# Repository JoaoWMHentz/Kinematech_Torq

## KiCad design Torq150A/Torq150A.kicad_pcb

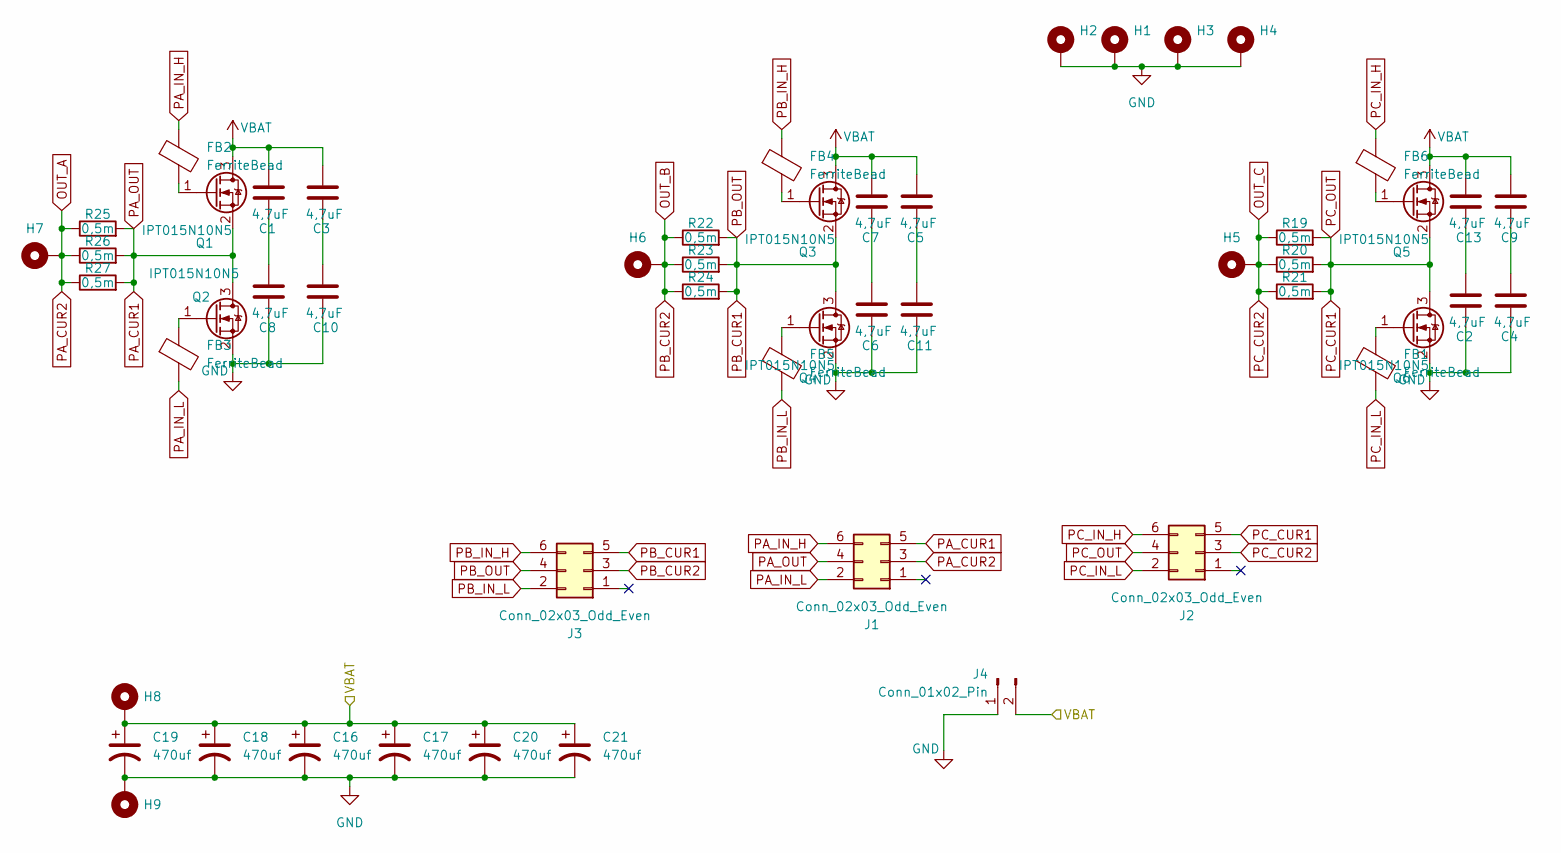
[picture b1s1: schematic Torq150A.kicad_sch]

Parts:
C1, C2, C3, C4, C5, C6, C7, C8, C9, C10, C11, C13: 4,7uF; C_1210_3225Metric
C16, C17, C18, C19, C20, C21: 470uf; CP_Radial_D16.0mm_P7.50mm
FB1, FB2, FB3, FB4, FB5, FB6: FerriteBead; L_Coilcraft_0805HQ_2012Metric
H1, H2, H3, H4: MountingHole_Pad; MountingHole_2.7mm_M2.5_ISO7380_Pad
H5, H6, H7, H8, H9: MountingHole_Pad; MountingHole_6.4mm_M6_Pad_Via
J1, J2, J3: Conn_02x03_Odd_Even; PinHeader_2x03_P2.54mm_Vertical
J4: Conn_01x02_Pin; PinSocket_1x02_P2.54mm_Vertical
Q1, Q2, Q3, Q4, Q5, Q6: IPT015N10N5; Infineon_PG-HSOF-8-1
R19, R20, R21, R22, R23, R24, R25, R26, R27: 0,5m; R_2512_6332Metric

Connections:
GND: C2.2, C4.2, C6.2, C8.2, C10.2, C11.2, C16.2, C17.2, C18.2, C19.2, C20.2, C21.2, H1.1, H2.1, H3.1, H4.1, H9.1, J4.1, Q2.2 (S), Q4.2 (S), Q6.2 (S)
unnamed: C1.2, C8.1
unnamed: C4.1, C9.2
unnamed: C6.1, C7.2
unnamed: C3.2, C10.1
unnamed: C5.2, C11.1
unnamed: C2.1, C13.2
unnamed: FB2.2, Q1.1 (G)
unnamed: FB3.1, Q2.1 (G)
unnamed: FB4.2, Q3.1 (G)
unnamed: FB5.1, Q4.1 (G)
unnamed: FB6.2, Q5.1 (G)
unnamed: FB1.1, Q6.1 (G)
OUT_A: H7.1, J1.3, R25.1, R26.1, R27.1
OUT_B: H6.1, J3.3, R22.1, R23.1, R24.1
OUT_C: H5.1, J2.3, R19.1, R20.1, R21.1
PA_CUR1: J1.4, J1.5, Q1.2 (S), Q2.3 (D), R25.2, R26.2, R27.2
PA_IN_H: FB2.1, J1.6
PA_IN_L: FB3.2, J1.2
PB_CUR1: J3.4, J3.5, Q3.2 (S), Q4.3 (D), R22.2, R23.2, R24.2
PB_IN_H: FB4.1, J3.6
PB_IN_L: FB5.2, J3.2
PC_CUR1: J2.4, J2.5, Q5.2 (S), Q6.3 (D), R19.2, R20.2, R21.2
PC_IN_H: FB6.1, J2.6
PC_IN_L: FB1.2, J2.2
VBAT: C1.1, C3.1, C5.1, C7.1, C9.1, C13.1, C16.1, C17.1, C18.1, C19.1, C20.1, C21.1, H8.1, J4.2, Q1.3 (D), Q3.3 (D), Q5.3 (D)

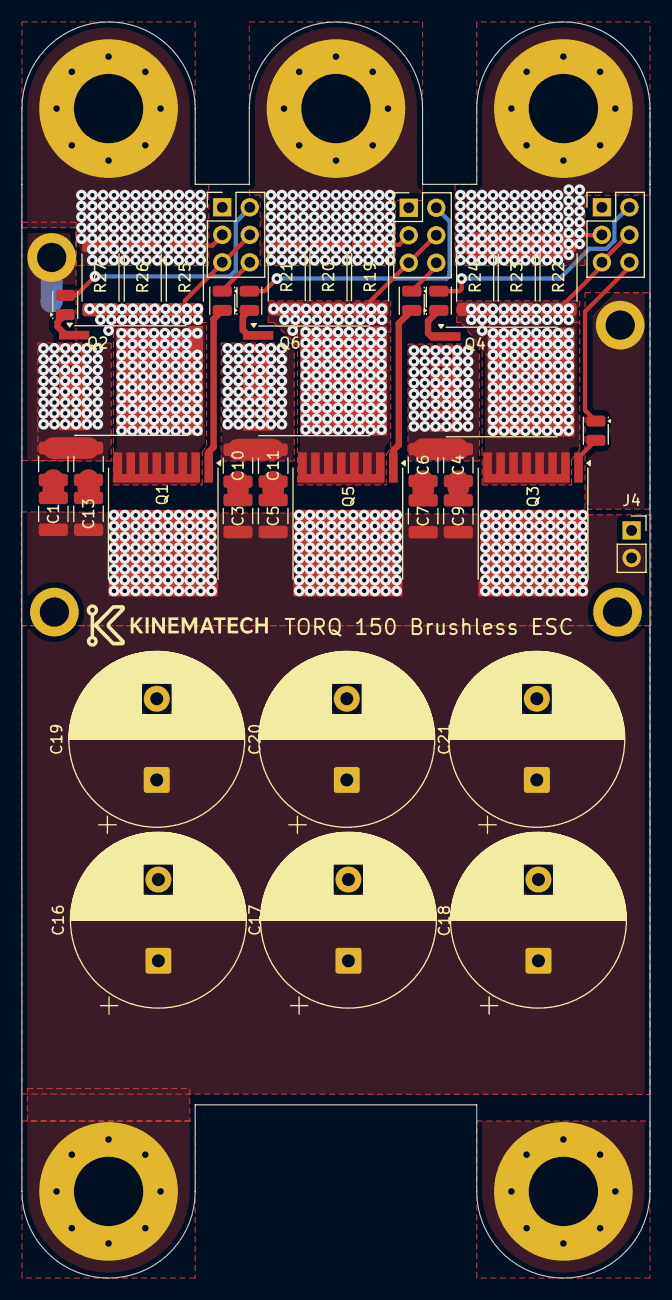
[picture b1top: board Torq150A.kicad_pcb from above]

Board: 2 copper layers, 58.0 x 116.0 mm, 52 parts (0 on the bottom side), 26 nets.

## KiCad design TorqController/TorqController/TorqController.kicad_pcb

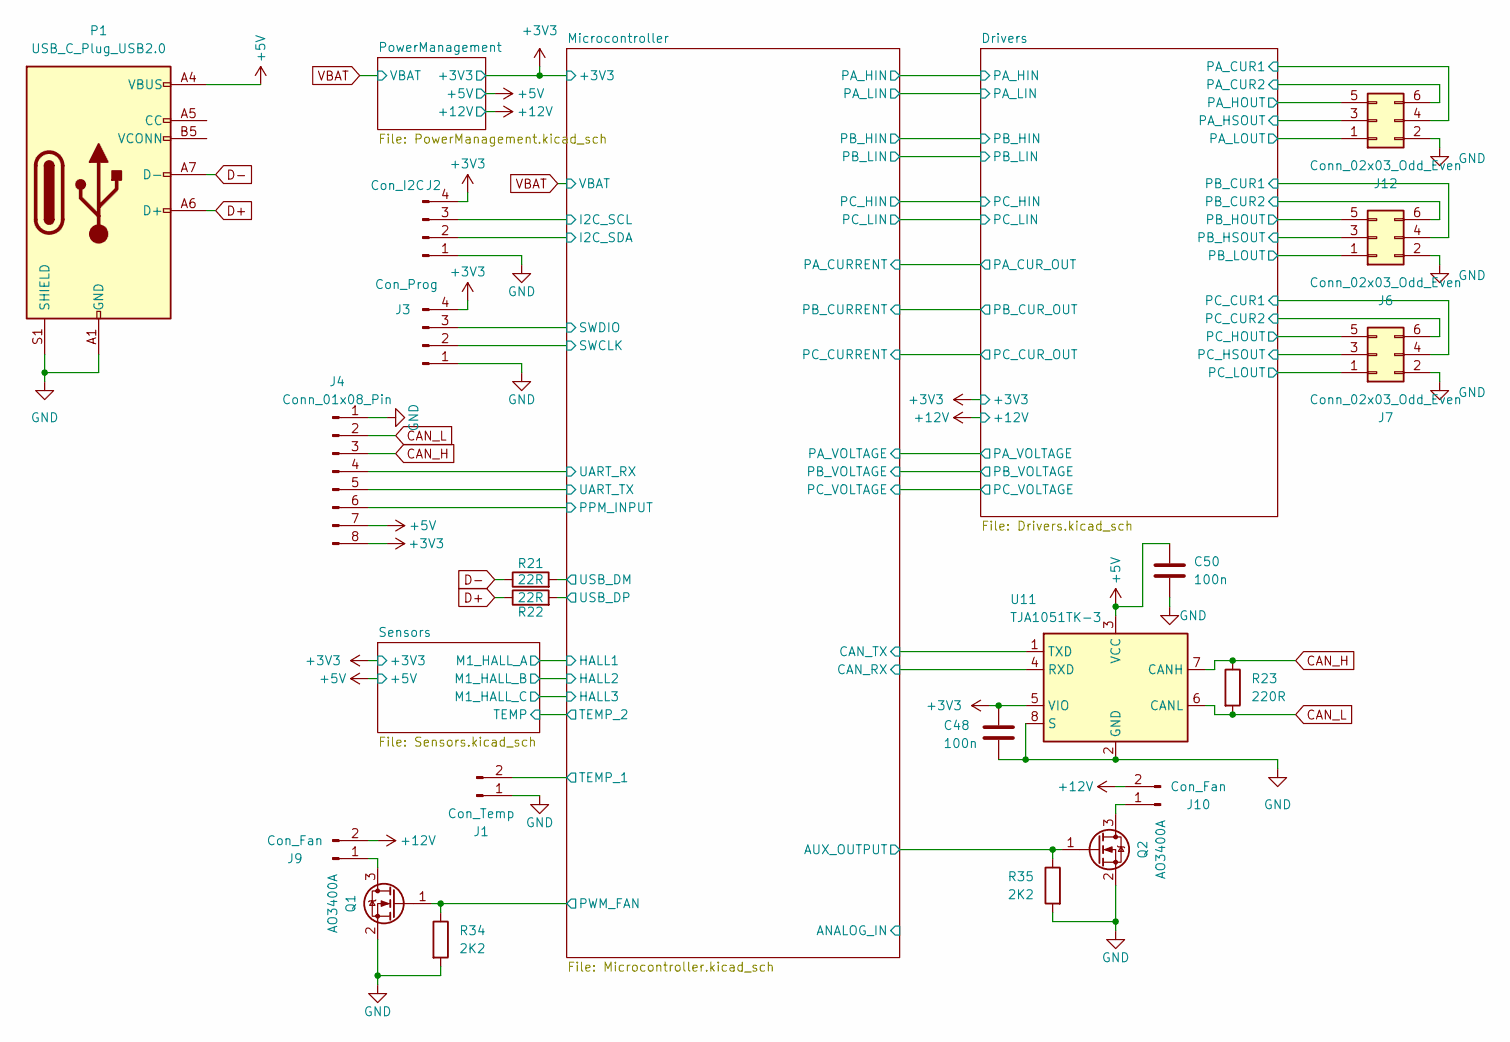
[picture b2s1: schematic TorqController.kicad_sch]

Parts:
C48, C50: 100n; C_0402_1005Metric
J1: Con_Temp; JST_EH_B2B-EH-A_1x02_P2.50mm_Vertical
J2: Con_I2C; JST_EH_B4B-EH-A_1x04_P2.50mm_Vertical
J3: Con_Prog; JST_EH_B4B-EH-A_1x04_P2.50mm_Vertical
J4: Conn_01x08_Pin; JST_EH_B8B-EH-A_1x08_P2.50mm_Vertical
J6, J7, J12: Conn_02x03_Odd_Even; PinHeader_2x03_P2.54mm_Vertical
J9, J10: Con_Fan; JST_EH_B2B-EH-A_1x02_P2.50mm_Vertical
P1: USB_C_Plug_USB2.0; USB_C_Receptacle_G-Switch_GT-USB-7010ASV
Q1, Q2: AO3400A; SOT-23
R21, R22: 22R; R_0402_1005Metric
R23: 220R; R_0402_1005Metric
R34, R35: 2K2; R_0402_1005Metric
U11: TJA1051TK-3; HVSON-8-1EP_3x3mm_P0.65mm_EP1.6x2.4mm

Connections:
+3V3: C48.1, J2.4, J3.4, J4.8, U11.5 (VIO); also elsewhere on the board
+5V: C50.1, J4.7, P1.A4 (VBUS), P1.A9 (VBUS), P1.B4 (VBUS), P1.B9 (VBUS), U11.3 (VCC); also elsewhere on the board
+12V: J9.2, J10.2; also elsewhere on the board
/Drivers/PA_CUR1: J12.4; also elsewhere on the board
/Drivers/PA_CUR2: J12.6; also elsewhere on the board
/Drivers/PA_HOUT: J12.5; also elsewhere on the board
/Drivers/PA_HSOUT: J12.3; also elsewhere on the board
/Drivers/PA_LOUT: J12.1; also elsewhere on the board
/Drivers/PB_CUR1: J6.4; also elsewhere on the board
/Drivers/PB_CUR2: J6.6; also elsewhere on the board
/Drivers/PB_HOUT: J6.5; also elsewhere on the board
/Drivers/PB_HSOUT: J6.3; also elsewhere on the board
/Drivers/PB_LOUT: J6.1; also elsewhere on the board
/Drivers/PC_CUR1: J7.4; also elsewhere on the board
/Drivers/PC_CUR2: J7.6; also elsewhere on the board
/Drivers/PC_HOUT: J7.5; also elsewhere on the board
/Drivers/PC_HSOUT: J7.3; also elsewhere on the board
/Drivers/PC_LOUT: J7.1; also elsewhere on the board
/Microcontroller/AUX_OUTPUT: Q2.1 (G), R35.1; also elsewhere on the board
/Microcontroller/CAN_RX: U11.4 (RXD); also elsewhere on the board
/Microcontroller/CAN_TX: U11.1 (TXD); also elsewhere on the board
/Microcontroller/I2C_SCL: J2.3; also elsewhere on the board
/Microcontroller/I2C_SDA: J2.2; also elsewhere on the board
/Microcontroller/PPM_INPUT: J4.6; also elsewhere on the board
/Microcontroller/PWM_FAN: Q1.1 (G), R34.1; also elsewhere on the board
/Microcontroller/SWCLK: J3.2; also elsewhere on the board
/Microcontroller/SWDIO: J3.3; also elsewhere on the board
/Microcontroller/UART_RX: J4.4; also elsewhere on the board
/Microcontroller/UART_TX: J4.5; also elsewhere on the board
/Microcontroller/USB_DM: R21.2; also elsewhere on the board
/Microcontroller/USB_DP: R22.2; also elsewhere on the board
CAN_H: J4.3, R23.1, U11.7 (CANH)
CAN_L: J4.2, R23.2, U11.6 (CANL)
D+: P1.A6 (D+), R22.1
D-: P1.A7 (D-), R21.1
GND: C48.2, C50.2, J1.1, J2.1, J3.1, J4.1, J6.2, J7.2, J12.2, P1.A1 (GND), P1.A12 (GND), P1.B1 (GND), P1.B12 (GND), P1.S1 (SHIELD), Q1.2 (S), Q2.2 (S), R34.2, R35.2, U11.2 (GND), U11.8 (S), U11.9 (GND); also elsewhere on the board
unnamed: J9.1, Q1.3 (D)
unnamed: J10.1, Q2.3 (D)
Temp_1: J1.2; also elsewhere on the board

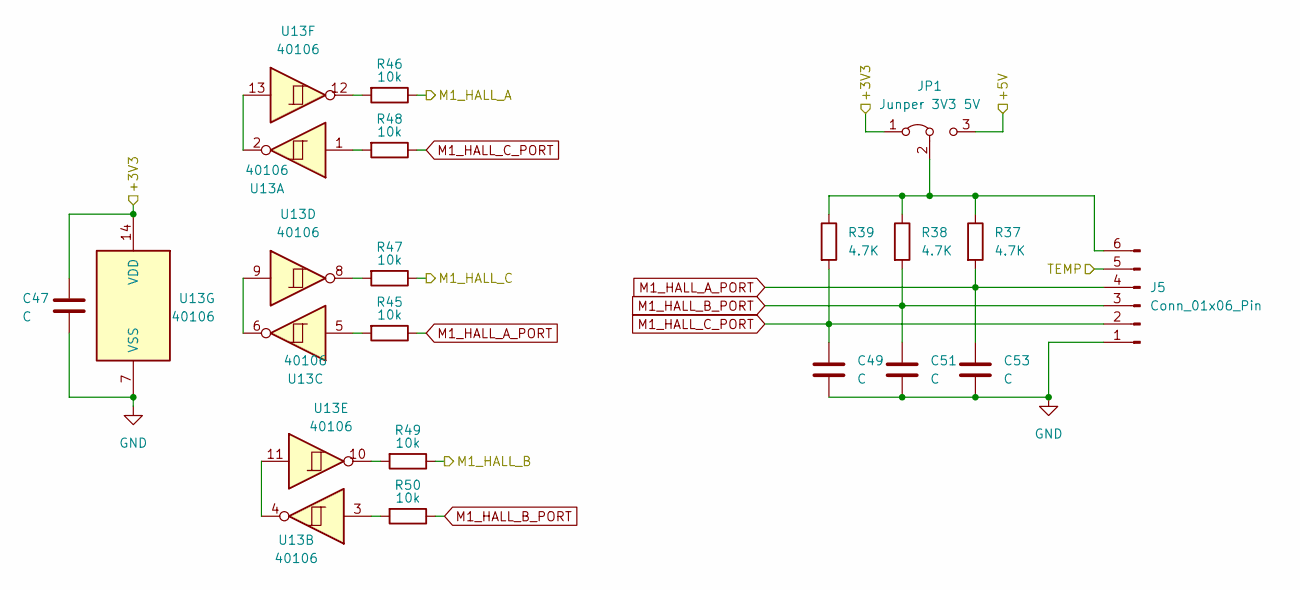
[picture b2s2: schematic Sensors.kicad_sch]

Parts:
C47, C49, C51, C53: C; C_0402_1005Metric
J5: Conn_01x06_Pin; JST_EH_B6B-EH-A_1x06_P2.50mm_Vertical
JP1: Junper 3V3 5V; SolderJumper-3_P1.3mm_Open_RoundedPad1.0x1.5mm_NumberLabels
R37, R38, R39: 4.7K; R_0402_1005Metric
R45, R46, R47, R48, R49, R50: 10k; R_0402_1005Metric
U13: 40106; DIP-14_W7.62mm_SMDSocket_SmallPads

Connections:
+3V3: C47.1, JP1.1 (A), U13.14 (VDD); also elsewhere on the board
/Microcontroller/HALL1: R46.1; also elsewhere on the board
/Microcontroller/HALL2: R49.1; also elsewhere on the board
/Microcontroller/HALL3: R47.1; also elsewhere on the board
GND: C47.2, C49.2, C51.2, C53.2, J5.1, U13.7 (VSS); also elsewhere on the board
M1_HALL_A_PORT: C53.1, J5.4, R37.2, R45.1
M1_HALL_B_PORT: C51.1, J5.3, R38.2, R50.1
M1_HALL_C_PORT: C49.1, J5.2, R39.2, R48.1
unnamed 60: J5.6, JP1.2 (C), R37.1, R38.1, R39.1; also elsewhere on the board
unnamed: R45.2, U13.5
unnamed: R46.2, U13.12
unnamed: R47.2, U13.8
unnamed: R48.2, U13.1
unnamed: R49.2, U13.10
unnamed: R50.2, U13.3
unnamed: U13.6, U13.9
unnamed: U13.4, U13.11
unnamed: U13.2, U13.13
Temp_2: J5.5; also elsewhere on the board

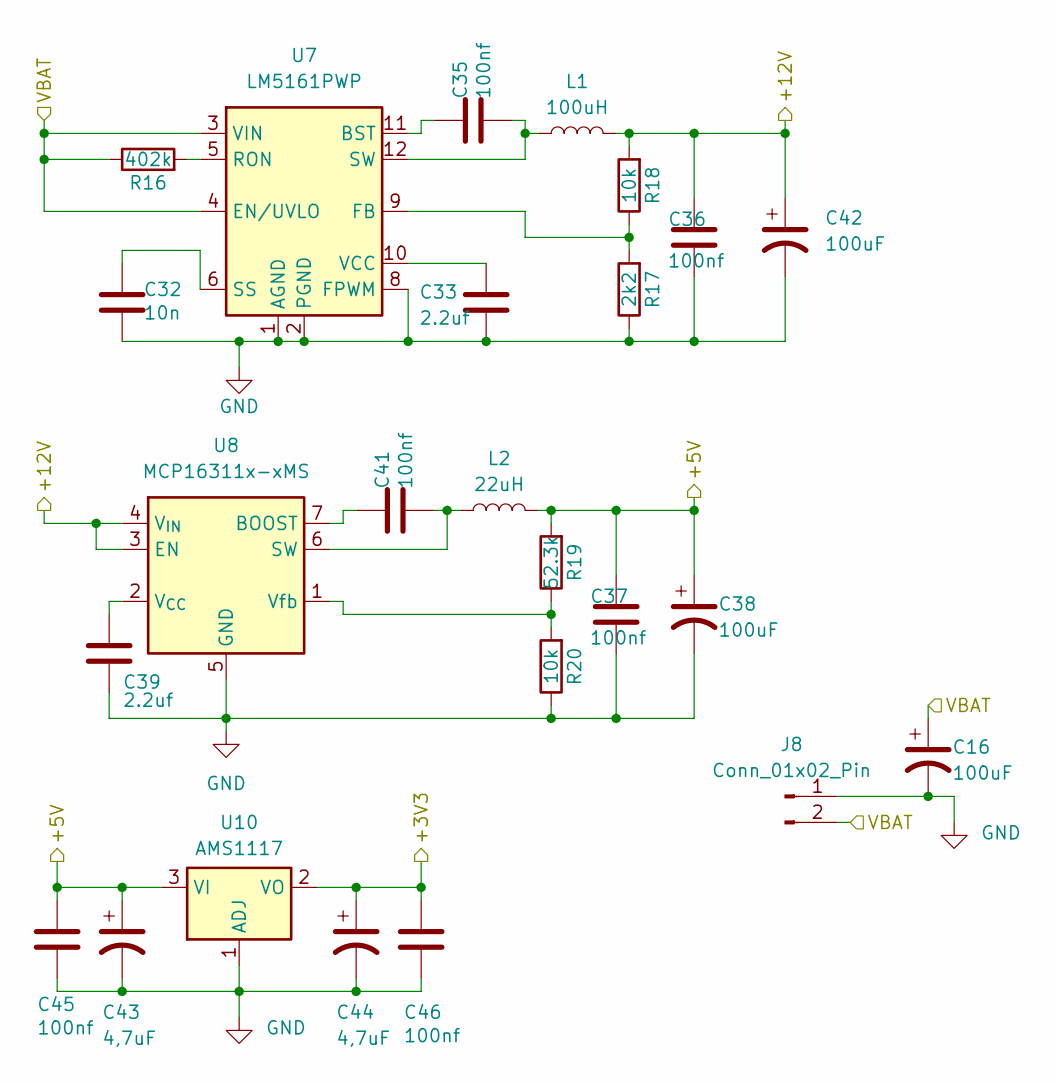
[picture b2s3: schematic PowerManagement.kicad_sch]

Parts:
C16, C38, C42: 100uF; CP_Elec_3x5.4
C32: 10n; C_0402_1005Metric
C33, C39: 2.2uf; C_0603_1608Metric
C35, C36, C37, C41, C45, C46: 100nf; C_0402_1005Metric
C43, C44: 4,7uF; CP_EIA-3216-10_Kemet-I
J8: Conn_01x02_Pin; PinHeader_1x02_P2.54mm_Vertical
L1: 100uH; L_KOHERelec_MDA5030
L2: 22uH; L_Chilisin_BMRB00050518-B
R16: 402k; R_0402_1005Metric
R17: 2k2; R_0402_1005Metric
R18, R20: 10k; R_0402_1005Metric
R19: 52.3k; R_0402_1005Metric
U7: LM5161PWP; Texas_HTSSOP-14-1EP_4.4x5mm_P0.65mm_EP3.4x5mm_Mask3.155x3.2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
U8: MCP16311x-xMS; MSOP-8_3x3mm_P0.65mm
U10: AMS1117; SOT-223-3_TabPin2

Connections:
+3V3: C44.1, C46.1, U10.2 (VO); also elsewhere on the board
+5V: C37.2, C38.1, C43.1, C45.1, L2.2, R19.2, U10.3 (VI); also elsewhere on the board
+12V: C36.2, C42.1, L1.2, R18.2, U8.3 (EN), U8.4 (V_{IN}); also elsewhere on the board
GND: C16.2, C32.2, C33.2, C36.1, C37.1, C38.2, C39.2, C42.2, C43.2, C44.2, C45.2, C46.2, J8.1, R17.1, R20.1, U7.1 (AGND), U7.2 (PGND), U7.8 (FPWM), U7.15 (AGND), U8.5 (GND), U8.8 (GND), U10.1 (ADJ); also elsewhere on the board
unnamed: C35.2, L1.1, U7.12 (SW), U7.13 (SW)
unnamed: C35.1, U7.11 (BST)
unnamed: R17.2, R18.1, U7.9 (FB)
unnamed: R16.2, U7.5 (RON)
unnamed: C32.1, U7.6 (SS)
unnamed: C33.1, U7.10 (VCC)
unnamed: C41.1, U8.7 (BOOST)
unnamed: C41.2, L2.1, U8.6 (SW)
unnamed: C39.1, U8.2 (V_{CC})
unnamed: R19.1, R20.2, U8.1 (Vfb)
VBAT: C16.1, J8.2, R16.1, U7.3 (VIN), U7.4 (EN/UVLO); also elsewhere on the board

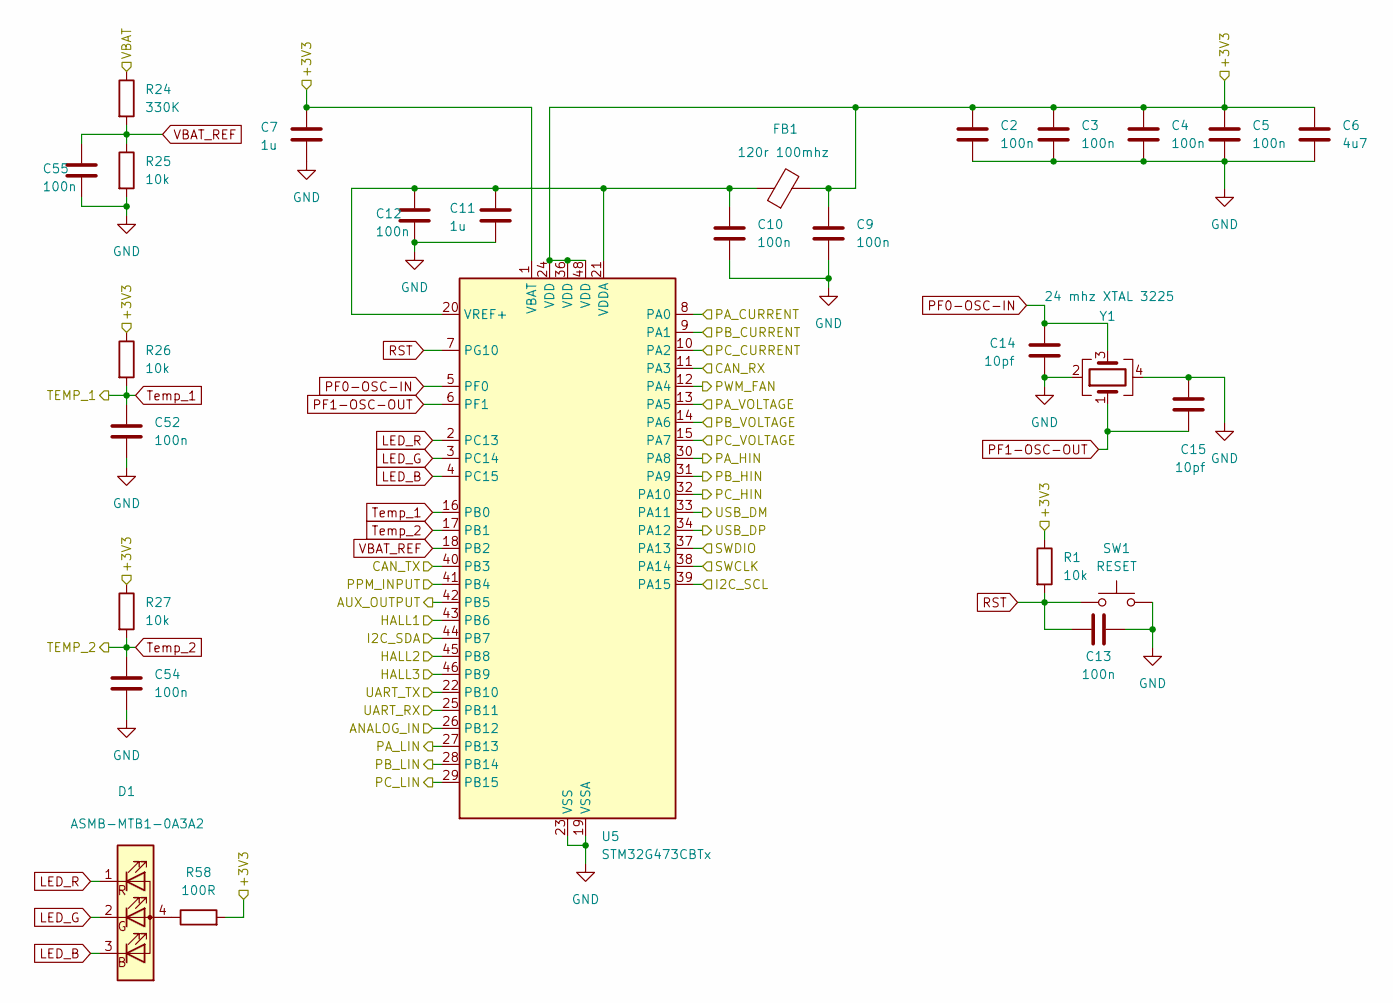
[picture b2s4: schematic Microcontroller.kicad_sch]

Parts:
C2, C3, C4, C5, C9, C10, C12, C13, C52, C54, C55: 100n; C_0402_1005Metric
C6: 4u7; C_0402_1005Metric
C7, C11: 1u; C_0402_1005Metric
C14, C15: 10pf; C_0402_1005Metric
D1: ASMB-MTB1-0A3A2; LED_Avago_PLCC4_3.2x2.8mm_CW
FB1: 120r 100mhz; L_0402_1005Metric
R1, R25, R26, R27: 10k; R_0402_1005Metric
R24: 330K; R_0402_1005Metric
R58: 100R; R_0603_1608Metric_Pad0.98x0.95mm_HandSolder
SW1: RESET; SW_SPST_B3U-1000P
U5: STM32G473CBTx; LQFP-48_7x7mm_P0.5mm
Y1: 24 mhz XTAL 3225; Crystal_SMD_2016-4Pin_2.0x1.6mm

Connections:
+3V3: C2.1, C3.1, C4.1, C5.1, C6.1, C7.1, C9.1, FB1.2, R1.1, R26.1, R27.1, R58.2, U5.1 (VBAT), U5.24 (VDD), U5.36 (VDD), U5.48 (VDD); also elsewhere on the board
/Drivers/PA_CUR_OUT: U5.8 (PA0); also elsewhere on the board
/Drivers/PA_HIN: U5.30 (PA8); also elsewhere on the board
/Drivers/PA_LIN: U5.27 (PB13); also elsewhere on the board
/Drivers/PA_VOLTAGE: U5.13 (PA5); also elsewhere on the board
/Drivers/PB_CUR_OUT: U5.9 (PA1); also elsewhere on the board
/Drivers/PB_HIN: U5.31 (PA9); also elsewhere on the board
/Drivers/PB_LIN: U5.28 (PB14); also elsewhere on the board
/Drivers/PB_VOLTAGE: U5.14 (PA6); also elsewhere on the board
/Drivers/PC_CUR_OUT: U5.10 (PA2); also elsewhere on the board
/Drivers/PC_HIN: U5.32 (PA10); also elsewhere on the board
/Drivers/PC_LIN: U5.29 (PB15); also elsewhere on the board
/Drivers/PC_VOLTAGE: U5.15 (PA7); also elsewhere on the board
/Microcontroller/ANALOG_IN: U5.26 (PB12)
/Microcontroller/AUX_OUTPUT: U5.42 (PB5); also elsewhere on the board
/Microcontroller/CAN_RX: U5.11 (PA3); also elsewhere on the board
/Microcontroller/CAN_TX: U5.40 (PB3); also elsewhere on the board
/Microcontroller/HALL1: U5.43 (PB6); also elsewhere on the board
/Microcontroller/HALL2: U5.45 (PB8); also elsewhere on the board
/Microcontroller/HALL3: U5.46 (PB9); also elsewhere on the board
/Microcontroller/I2C_SCL: U5.39 (PA15); also elsewhere on the board
/Microcontroller/I2C_SDA: U5.44 (PB7); also elsewhere on the board
/Microcontroller/PPM_INPUT: U5.41 (PB4); also elsewhere on the board
/Microcontroller/PWM_FAN: U5.12 (PA4); also elsewhere on the board
/Microcontroller/SWCLK: U5.38 (PA14); also elsewhere on the board
/Microcontroller/SWDIO: U5.37 (PA13); also elsewhere on the board
/Microcontroller/UART_RX: U5.25 (PB11); also elsewhere on the board
/Microcontroller/UART_TX: U5.22 (PB10); also elsewhere on the board
/Microcontroller/USB_DM: U5.33 (PA11); also elsewhere on the board
/Microcontroller/USB_DP: U5.34 (PA12); also elsewhere on the board
GND: C2.2, C3.2, C4.2, C5.2, C6.2, C7.2, C9.2, C10.2, C11.2, C12.2, C13.2, C14.2, C15.1, C52.2, C54.2, C55.2, R25.2, SW1.2, U5.19 (VSSA), U5.23 (VSS), U5.35 (VSS), U5.47 (VSS), Y1.2, Y1.4; also elsewhere on the board
LED_B: D1.3 (BK), U5.4 (PC15)
LED_G: D1.2 (GK), U5.3 (PC14)
LED_R: D1.1 (RK), U5.2 (PC13)
unnamed: D1.4 (A), R58.1
unnamed: C10.1, C11.1, C12.1, FB1.1, U5.20 (VREF+), U5.21 (VDDA)
PF0-OSC-IN: C14.1, U5.5 (PF0), Y1.3
PF1-OSC-OUT: C15.2, U5.6 (PF1), Y1.1
RST: C13.1, R1.2, SW1.1, U5.7 (PG10)
Temp_1: C52.1, R26.2, U5.16 (PB0); also elsewhere on the board
Temp_2: C54.1, R27.2, U5.17 (PB1); also elsewhere on the board
VBAT: R24.1; also elsewhere on the board
VBAT_REF: C55.1, R24.2, R25.1, U5.18 (PB2)

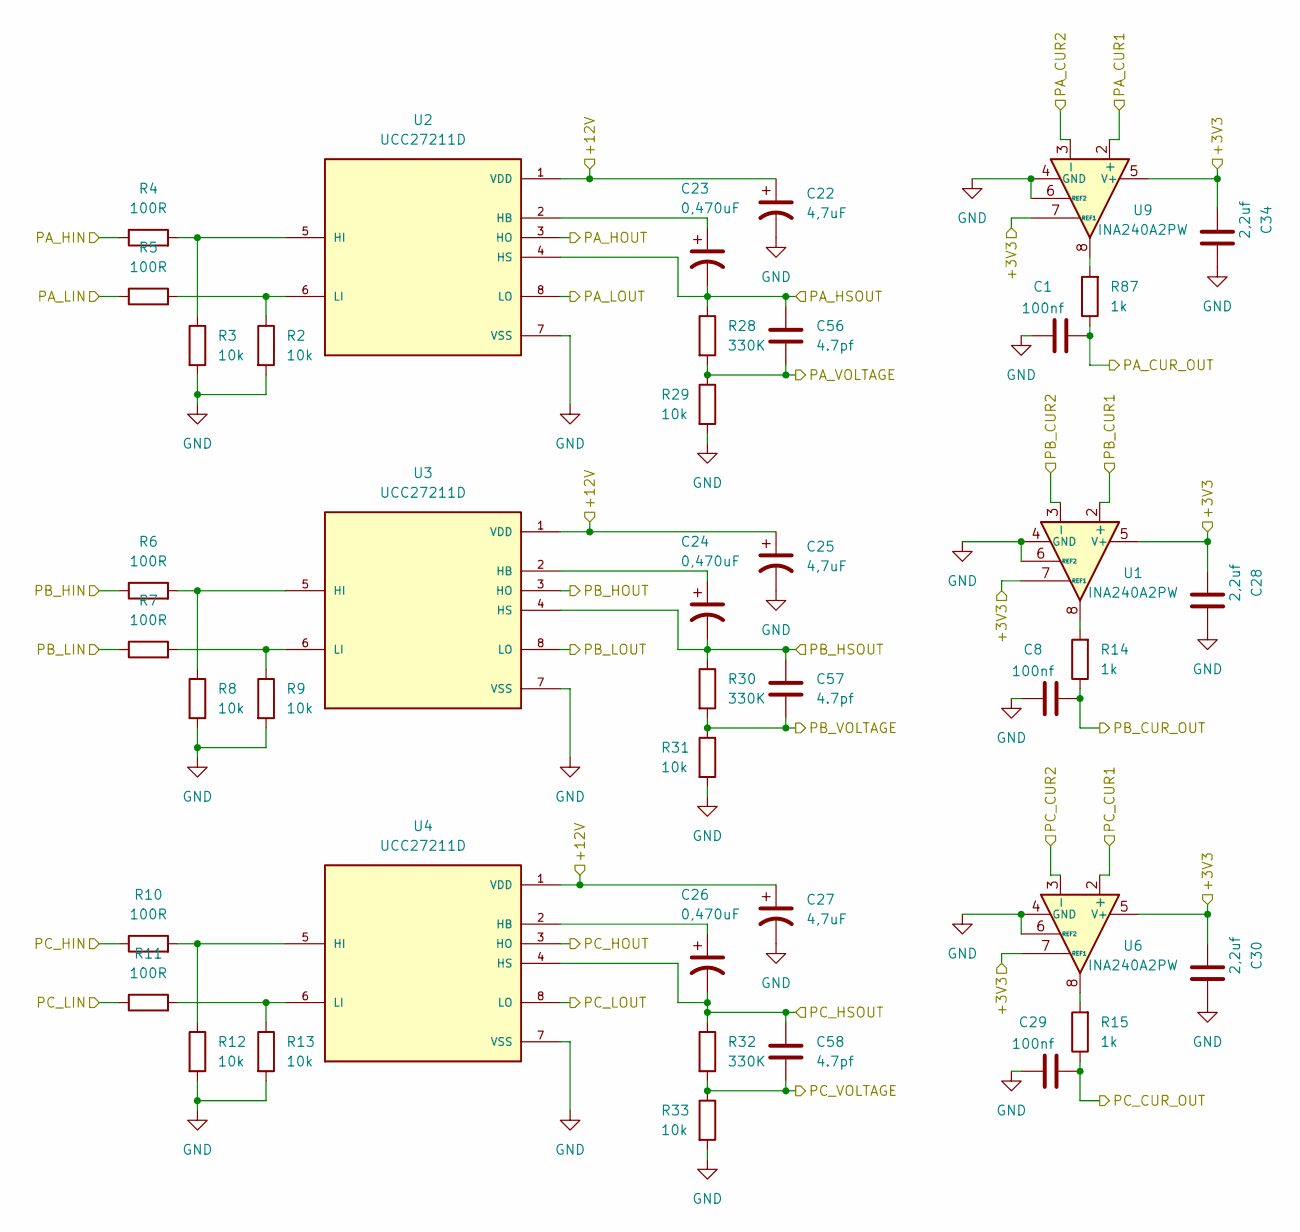
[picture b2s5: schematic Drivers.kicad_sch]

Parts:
C1, C8, C29: 100nf; C_0402_1005Metric
C22, C25, C27: 4,7uF; CP_EIA-3216-10_Kemet-I
C23, C24, C26: 0,470uF; CP_EIA-3216-10_Kemet-I
C28, C30, C34: 2,2uf; C_0402_1005Metric
C56, C57, C58: 4.7pf; C_0402_1005Metric
R2, R3, R8, R9, R12, R13, R29, R31, R33: 10k; R_0402_1005Metric
R4, R5, R6, R7, R10, R11: 100R; R_0402_1005Metric
R14, R15, R87: 1k; R_0402_1005Metric
R28, R30, R32: 330K; R_0402_1005Metric
U1, U6, U9: INA240A2PW; TSSOP-8_4.4x3mm_P0.65mm
U2, U3, U4: UCC27211D; HSOP-8-1EP_3.9x4.9mm_P1.27mm_EP2.41x3.1mm_ThermalVias; PARTREV F

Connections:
+3V3: C28.1, C30.1, C34.1, U1.5 (V+), U1.7 (REF1), U6.5 (V+), U6.7 (REF1), U9.5 (V+), U9.7 (REF1); also elsewhere on the board
+12V: C22.1, C25.1, C27.1, U2.1 (VDD), U3.1 (VDD), U4.1 (VDD); also elsewhere on the board
/Drivers/PA_CUR1: U9.2 (+); also elsewhere on the board
/Drivers/PA_CUR2: U9.3 (-); also elsewhere on the board
/Drivers/PA_CUR_OUT: C1.2, R87.1; also elsewhere on the board
/Drivers/PA_HIN: R4.1; also elsewhere on the board
/Drivers/PA_HOUT: U2.3 (HO); also elsewhere on the board
/Drivers/PA_HSOUT: C23.2, C56.1, R28.1, U2.4 (HS); also elsewhere on the board
/Drivers/PA_LIN: R5.1; also elsewhere on the board
/Drivers/PA_LOUT: U2.8 (LO); also elsewhere on the board
/Drivers/PA_VOLTAGE: C56.2, R28.2, R29.1; also elsewhere on the board
/Drivers/PB_CUR1: U1.2 (+); also elsewhere on the board
/Drivers/PB_CUR2: U1.3 (-); also elsewhere on the board
/Drivers/PB_CUR_OUT: C8.2, R14.1; also elsewhere on the board
/Drivers/PB_HIN: R6.1; also elsewhere on the board
/Drivers/PB_HOUT: U3.3 (HO); also elsewhere on the board
/Drivers/PB_HSOUT: C24.2, C57.1, R30.1, U3.4 (HS); also elsewhere on the board
/Drivers/PB_LIN: R7.1; also elsewhere on the board
/Drivers/PB_LOUT: U3.8 (LO); also elsewhere on the board
/Drivers/PB_VOLTAGE: C57.2, R30.2, R31.1; also elsewhere on the board
/Drivers/PC_CUR1: U6.2 (+); also elsewhere on the board
/Drivers/PC_CUR2: U6.3 (-); also elsewhere on the board
/Drivers/PC_CUR_OUT: C29.2, R15.1; also elsewhere on the board
/Drivers/PC_HIN: R10.1; also elsewhere on the board
/Drivers/PC_HOUT: U4.3 (HO); also elsewhere on the board
/Drivers/PC_HSOUT: C26.2, C58.1, R32.1, U4.4 (HS); also elsewhere on the board
/Drivers/PC_LIN: R11.1; also elsewhere on the board
/Drivers/PC_LOUT: U4.8 (LO); also elsewhere on the board
/Drivers/PC_VOLTAGE: C58.2, R32.2, R33.1; also elsewhere on the board
GND: C1.1, C8.1, C22.2, C25.2, C27.2, C28.2, C29.1, C30.2, C34.2, R2.2, R3.2, R8.2, R9.2, R12.2, R13.2, R29.2, R31.2, R33.2, U1.1 (GND), U1.4 (GND), U1.6 (REF2), U2.7 (VSS), U3.7 (VSS), U4.7 (VSS), U6.1 (GND), U6.4 (GND), U6.6 (REF2), U9.1 (GND), U9.4 (GND), U9.6 (REF2); also elsewhere on the board
unnamed: R14.2, U1.8
unnamed: R15.2, U6.8
unnamed: R87.2, U9.8
unnamed: C23.1, U2.2 (HB)
unnamed: R3.1, R4.2, U2.5 (HI)
unnamed: R2.1, R5.2, U2.6 (LI)
unnamed: C24.1, U3.2 (HB)
unnamed: R6.2, R8.1, U3.5 (HI)
unnamed: R7.2, R9.1, U3.6 (LI)
unnamed: C26.1, U4.2 (HB)
unnamed: R10.2, R12.1, U4.5 (HI)
unnamed: R11.2, R13.1, U4.6 (LI)

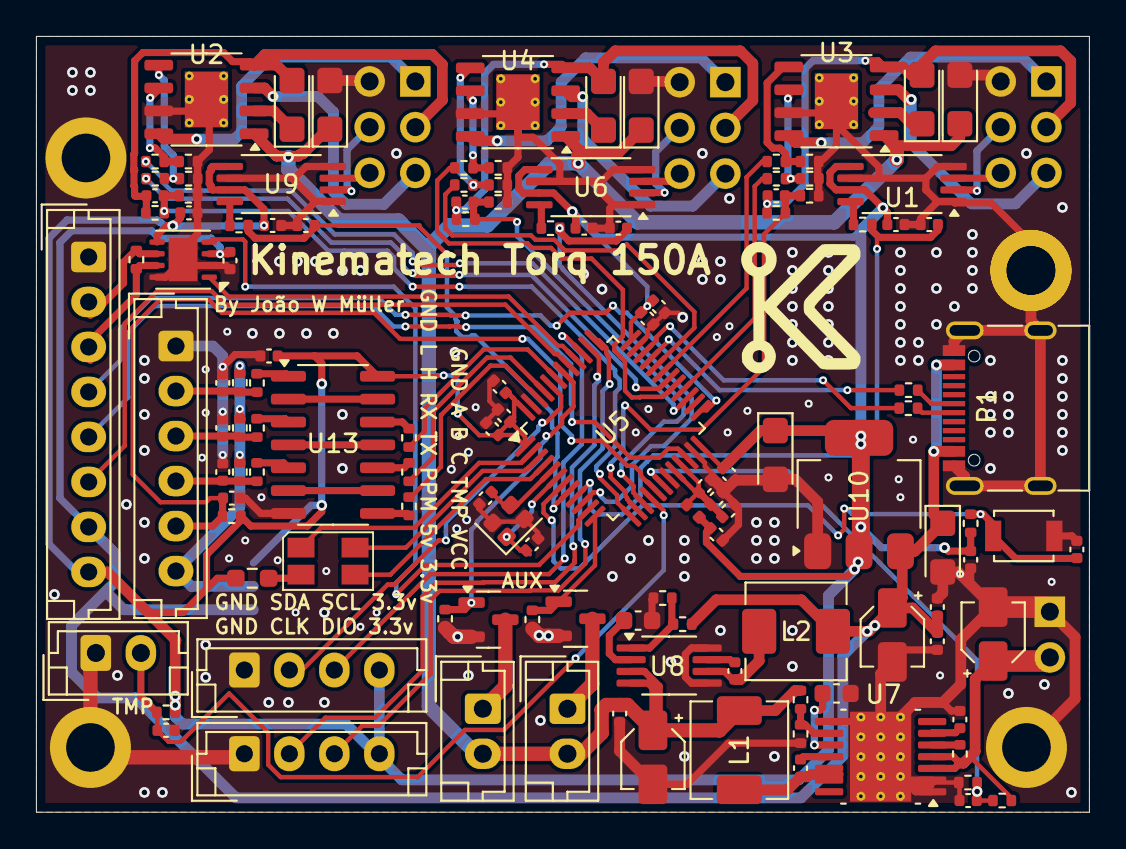
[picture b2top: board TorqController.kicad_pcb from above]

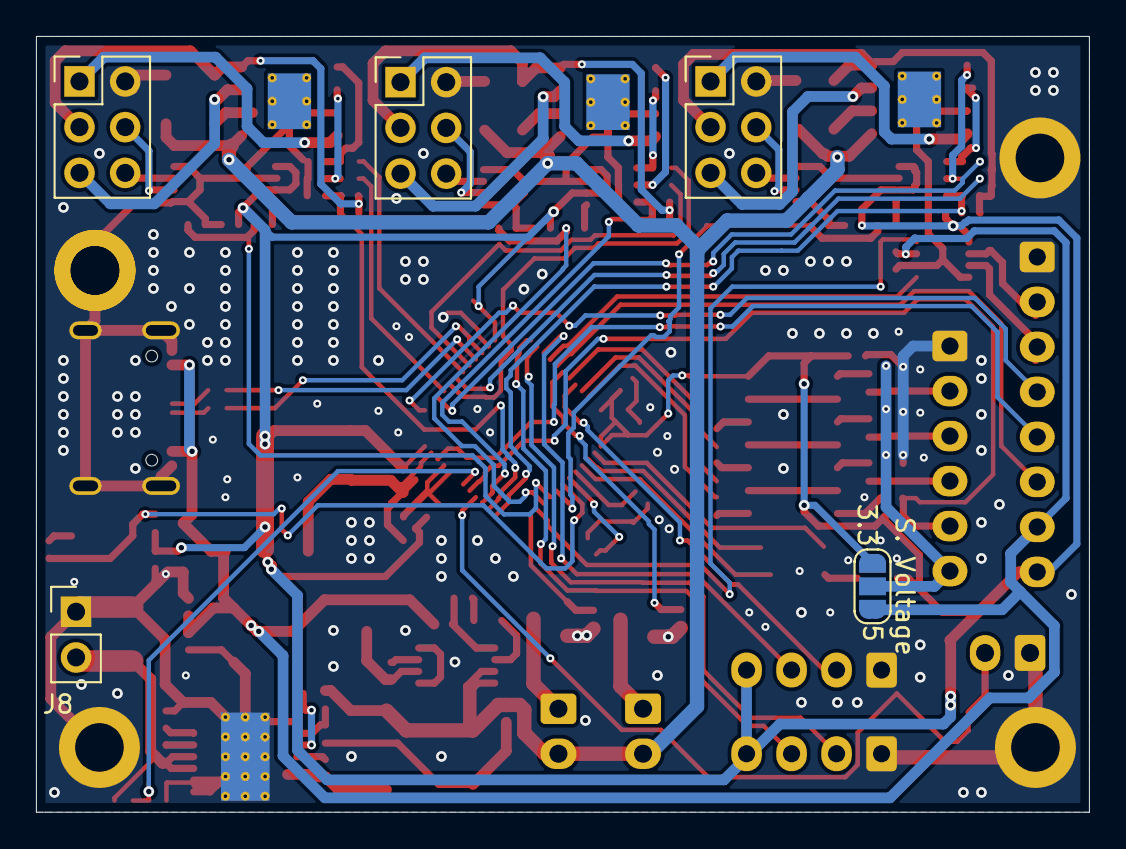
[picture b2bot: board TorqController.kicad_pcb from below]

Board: 2 copper layers, 58.5 x 43.1 mm, 132 parts (5 on the bottom side), 100 nets.

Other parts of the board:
H2, H4: MountingHole_Pad; MountingHole_2.7mm_M2.5_ISO7380_Pad
S. Voltage: Junper 3V3 5V; SolderJumper-3_P1.3mm_Open_RoundedPad1.0x1.5mm_NumberLabels

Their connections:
+3V3: S. Voltage.1 (A); also elsewhere on the board
+5V: S. Voltage.3 (B); also elsewhere on the board
GND: H2.1, H4.1; also elsewhere on the board
unnamed 60: S. Voltage.2 (C); also elsewhere on the board

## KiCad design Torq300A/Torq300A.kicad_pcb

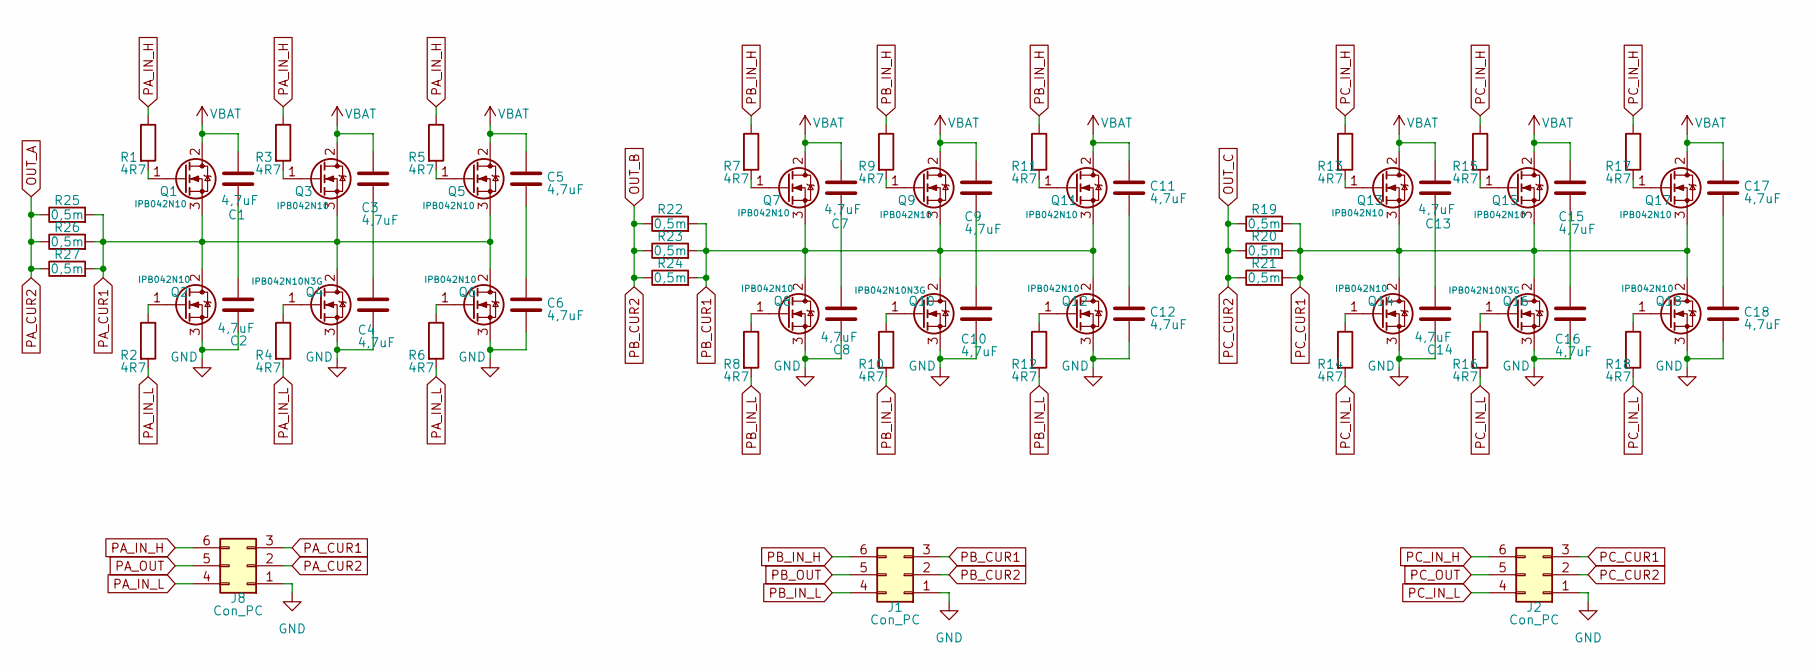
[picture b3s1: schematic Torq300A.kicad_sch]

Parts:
C1, C2, C3, C4, C5, C6, C7, C8, C9, C10, C11, C12, C13, C14, C15, C16, C17, C18: 4,7uF; C_1210_3225Metric
J1, J2, J8: Con_PC; PinHeader_2x03_P2.54mm_Vertical
Q1, Q2, Q3, Q5, Q6, Q7, Q8, Q9, Q11, Q12, Q13, Q14, Q15, Q17, Q18: IPB042N10; TO-263-2
Q4, Q10, Q16: IPB042N10N3G; TO-263-2
R1, R2, R3, R4, R5, R6, R7, R8, R9, R10, R11, R12, R13, R14, R15, R16, R17, R18: 4R7; R_0603_1608Metric
R19, R20, R21, R22, R23, R24, R25, R26, R27: 0,5m; R_2512_6332Metric

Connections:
GND: C2.2, C4.2, C6.2, C8.2, C10.2, C12.2, C14.2, C16.2, C18.2, J1.1, J2.1, J8.1, Q2.3 (S), Q4.3 (S), Q6.3 (S), Q8.3 (S), Q10.3 (S), Q12.3 (S), Q14.3 (S), Q16.3 (S), Q18.3 (S)
unnamed: C1.2, C2.1
unnamed: C3.2, C4.1
unnamed: C5.2, C6.1
unnamed: C7.2, C8.1
unnamed: C9.2, C10.1
unnamed: C11.2, C12.1
unnamed: C13.2, C14.1
unnamed: C15.2, C16.1
unnamed: C17.2, C18.1
unnamed: Q1.1 (G), R1.2
unnamed: Q2.1 (G), R2.1
unnamed: Q3.1 (G), R3.2
unnamed: Q4.1 (G), R4.1
unnamed: Q5.1 (G), R5.2
unnamed: Q6.1 (G), R6.1
unnamed: Q7.1 (G), R7.2
unnamed: Q8.1 (G), R8.1
unnamed: Q9.1 (G), R9.2
unnamed: Q10.1 (G), R10.1
unnamed: Q11.1 (G), R11.2
unnamed: Q12.1 (G), R12.1
unnamed: Q13.1 (G), R13.2
unnamed: Q14.1 (G), R14.1
unnamed: Q15.1 (G), R15.2
unnamed: Q16.1 (G), R16.1
unnamed: Q17.1 (G), R17.2
unnamed: Q18.1 (G), R18.1
OUT_A: J8.2, R25.1, R26.1, R27.1
OUT_B: J1.2, R22.1, R23.1, R24.1
OUT_C: J2.2, R19.1, R20.1, R21.1
PA_CUR1: J8.3, Q1.3 (S), Q2.2 (D), Q3.3 (S), Q4.2 (D), Q5.3 (S), Q6.2 (D), R25.2, R26.2, R27.2
PA_IN_H: J8.6, R1.1, R3.1, R5.1
PA_IN_L: J8.4, R2.2, R4.2, R6.2
PA_OUT: J8.5
PB_CUR1: J1.3, Q7.3 (S), Q8.2 (D), Q9.3 (S), Q10.2 (D), Q11.3 (S), Q12.2 (D), R22.2, R23.2, R24.2
PB_IN_H: J1.6, R7.1, R9.1, R11.1
PB_IN_L: J1.4, R8.2, R10.2, R12.2
PB_OUT: J1.5
PC_CUR1: J2.3, Q13.3 (S), Q14.2 (D), Q15.3 (S), Q16.2 (D), Q17.3 (S), Q18.2 (D), R19.2, R20.2, R21.2
PC_IN_H: J2.6, R13.1, R15.1, R17.1
PC_IN_L: J2.4, R14.2, R16.2, R18.2
PC_OUT: J2.5
VBAT: C1.1, C3.1, C5.1, C7.1, C9.1, C11.1, C13.1, C15.1, C17.1, Q1.2 (D), Q3.2 (D), Q5.2 (D), Q7.2 (D), Q9.2 (D), Q11.2 (D), Q13.2 (D), Q15.2 (D), Q17.2 (D)

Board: 2 copper layers, 66 parts (0 on the bottom side), 41 nets, no tracks yet.

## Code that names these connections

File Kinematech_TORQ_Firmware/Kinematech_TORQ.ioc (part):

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Mcu.Name=STM32G473C(B-C-E)Tx
Mcu.Package=LQFP48
Mcu.UserName=STM32G473CBTx
PA0.Mode=IN1-Single-Ended
PA0.Signal=ADC1_IN1
PA1.Mode=IN2-Single-Ended
PA1.Signal=ADC1_IN2
PA10.Signal=S_TIM1_CH3
PA11.Mode=Device
PA11.Signal=USB_DM
PA12.Mode=Device
PA12.Signal=USB_DP
PA13.Mode=Serial_Wire
PA13.Signal=SYS_JTMS-SWDIO
PA14.Mode=Serial_Wire
PA14.Signal=SYS_JTCK-SWCLK
PA15.Mode=I2C
PA15.Signal=I2C1_SCL
PA2.Mode=IN3-Single-Ended
PA2.Signal=ADC1_IN3
PA3.Signal=S_TIM2_CH4
PA4.Signal=S_TIM3_CH2
PA5.Mode=IN13-Single-Ended
PA5.Signal=ADC2_IN13
PA6.Mode=IN3-Single-Ended
PA6.Signal=ADC2_IN3
PA7.Mode=IN4-Single-Ended
PA7.Signal=ADC2_IN4
PA8.Signal=S_TIM1_CH1
PA9.Signal=S_TIM1_CH2
PB0.Mode=IN12-Single-Ended
PB0.Signal=ADC3_IN12
PB1.Mode=IN1-Single-Ended
PB1.Signal=ADC3_IN1
PB10.Mode=Asynchronous
PB10.Signal=USART3_TX
PB11.Mode=Asynchronous
PB11.Signal=USART3_RX
PB12.Mode=IN3-Single-Ended
PB12.Signal=ADC4_IN3
PB13.Mode=PWM Generation1 CH1 CH1N
PB13.Signal=TIM1_CH1N
PB14.Mode=PWM Generation2 CH2 CH2N
PB14.Signal=TIM1_CH2N
PB15.Mode=PWM Generation3 CH3 CH3N
PB15.Signal=TIM1_CH3N
PB2.Mode=IN12-Single-Ended
PB2.Signal=ADC2_IN12
PB3.Mode=Asynchronous
PB3.Signal=USART2_TX
PB4.Mode=Asynchronous
PB4.Signal=USART2_RX
PB5.Signal=S_TIM17_CH1
PB6.Signal=S_TIM8_CH1
PB7.Mode=I2C
PB7.Signal=I2C1_SDA
PB8-BOOT0.Signal=S_TIM8_CH2
PB9.Signal=S_TIM8_CH3
PC13.Signal=GPIO_Output
PC14-OSC32_IN.Signal=GPIO_Output
PC15-OSC32_OUT.Signal=GPIO_Output
PF0-OSC_IN.Signal=EVENTOUT
PF1-OSC_OUT.Signal=EVENTOUT
PG10-NRST.Signal=EVENTOUT
RCC.HSE_VALUE=8000000
RCC.SYSCLKFreq_VALUE=16000000
board=custom

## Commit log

2025-09-20 Add lock files for PCB and schematic with user information
